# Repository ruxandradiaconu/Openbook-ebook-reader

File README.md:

OpenBook e-book reader
Diaconu Oana-Ruxandra - 331CC

## Diagrama bloc

## BOM – Bill of Materials

| Componenta                                                | Link                                                                                             | Datasheet                                                                                                                              |
|:----------------------------------------------------------|:-------------------------------------------------------------------------------------------------|:---------------------------------------------------------------------------------------------------------------------------------------|
| 112A-TAAR-R03_ATTEND                                      | https://store.comet.bg/en/Catalogue/Product/43497/                                               | https://store.comet.bg/en/Catalogue/Product/43497/                                                                                     |
| 744043680IND_4828-WE-TPC_WRE                              | https://www.digikey.sg/en/models/1638515                                                         | https://www.digikey.sg/en/models/1638515                                                                                               |
| ADAFRUIT_LEDCHIP-LED0603                                  | https://www.snapeda.com/parts/KP-1608SURCK/Kingbright/view-part/?ref=search&t=LED%200603         | https://www.snapeda.com/parts/KP-1608SURCK/Kingbright/datasheet/                                                                       |
| BD5229G-TR                                                | https://componentsearchengine.com/part-view/BD5229G-TR/ROHM%20Semiconductor                      | https://componentsearchengine.com/part-view/BD5229G-TR/ROHM%20Semiconductor                                                            |
| BME680                                                    | https://www.snapeda.com/parts/BME680/Bosch/view-part/?welcome=home                               | https://www.snapeda.com/parts/BME680/Bosch%20Sensortec/datasheet/                                                                      |
| BUTTON_CUSYOMV1                                           | https://industry.panasonic.com/global/en/downloads?tab=cad&small_g_cd=203&part_no=EVQPUJ02K      | https://industry.panasonic.com/global/en/downloads?tab=catalog&small_g_cd=203&part_no=EVQPUJ02K                                        |
| CC0402MRX5R5BB106                                           | https://componentsearchengine.com/part-view/CC0402MRX5R5BB106/YAGEO      | https://componentsearchengine.com/part-view/CC0402MRX5R5BB106/YAGEO                                        |
| CPH3225A                                                  | https://www.snapeda.com/parts/CPH3225A/Seiko+Instruments/view-part/?ref=eda                      | https://www.snapeda.com/parts/CPH3225A/Seiko%20Instruments/datasheet/                                                                  |
| DS3231SN                                                  | https://www.snapeda.com/parts/DS3231SN%23/Analog+Devices/view-part/?ref=eda                      | https://www.snapeda.com/parts/DS3231SN%23/Analog%20Devices/datasheet/                                                                  |
| 7.5in E-ink Display                                                  | https://grabcad.com/library/7-5in-e-ink-display-assortment-1                      | https://grabcad.com/library/7-5in-e-ink-display-assortment-1                                                                  |
| ESP32-C6-WROOM-1-N8                                       | https://www.snapeda.com/parts/ESP32-C6-WROOM-1-N8/Espressif+Systems/view-part/?ref=eda           | https://www.snapeda.com/parts/ESP32-C6-WROOM-1-N8/Espressif%20Systems/datasheet/                                                       |
| ESP32C6_VARISTORCN1812                                    | https://www.mouser.co.uk/ProductDetail/EPCOS-TDK/B72520T0350K062                                 | https://www.mouser.co.uk/ProductDetail/EPCOS-TDK/B72520T0350K062                                                      |
| ESP32_WROVER_BME680_BME680                                | https://www.snapeda.com/parts/BME680/Bosch/view-part/?welcome=home                               | https://www.snapeda.com/parts/BME680/Bosch%20Sensortec/datasheet/                                                                      |
| ESP32_WROVER_EAGLE-LTSPICE_CC0402                         | https://componentsearchengine.com/part-view/CC0402MRX5R5BB106/YAGEO                              | https://componentsearchengine.com/Datasheets/2/CC0402MRX5R5BB106.pdf                                                                   |
| ESP32_WROVER_EAGLE-LTSPICE_RR0402                         | https://www.snapeda.com/parts/RC0402FR-07226RL/Yageo/view-part/                                  | https://www.snapeda.com/parts/RC0402FR-07226RL/Yageo/datasheet/                                                                        |
| ESP32_WROVER_SPARKFUN-DISCRETESEMI_MOSFET_PCH-DMG2305UX-7 | https://componentsearchengine.com/part-view/DMG2305UX-7/Diodes%20Incorporated                    | https://componentsearchengine.com/part-view/DMG2305UX-7/Diodes%20Incorporated                                                                                |
| FH34SRJ-24S-0.5SH_99_                                     | https://componentsearchengine.com/part-view/XC6220A331MR-G/Torex                                 |  https://componentsearchengine.com/part-view/XC6220A331MR-G/Torex                                                                           |
| MAX17048G+T10                                             | https://www.snapeda.com/parts/MAX17048G+T10/Analog+Devices/view-part/?ref=eda                    | https://www.snapeda.com/parts/MAX17048G+T10/Analog%20Devices/datasheet/                                                                |
| MBR0530                                                   | https://ro.mouser.com/ProductDetail/KYOCERA-AVX/SD0805S020S1R0                                   | https://ro.mouser.com/datasheet/2/40/schottky-3165252.pdf                                                                              |
| MCP73831                                                  | https://www.digikey.com/en/models/1874108                                                        | https://www.digikey.com/en/models/1874108 |
| PGB1010603MR                                              | https://www.snapeda.com/parts/PGB1010603MR/Littelfuse/view-part/?ref=eda                         | https://www.snapeda.com/parts/PGB1010603MR/Littelfuse%20Inc./datasheet/                                                                |
| QWIIC_CONNECTORJS-1MM                                     | https://www.snapeda.com/parts/PRT-14417/SparkFun/view-part/                                      | https://www.snapeda.com/parts/PRT-14417/SparkFun%20Electronics/datasheet/                                                              |
| RCL-CT3528                              | https://stud33302.autodesk360.com/g/shares/SH30dd5QT870c25f12fc6065d74bcaa3bf24                                                         | https://stud33302.autodesk360.com/g/shares/SH30dd5QT870c25f12fc6065d74bcaa3bf24                                                                                               |
| SAMACSYS_PARTS_USB4110-GF-A                               | https://componentsearchengine.com/part-view/USB4110-GF-A/GCT%20(GLOBAL%20CONNECTOR%20TECHNOLOGY) | https://componentsearchengine.com/part-view/USB4110-GF-A/GCT%20(GLOBAL%20CONNECTOR%20TECHNOLOGY)                                                                                              |
| SI1308EDL-T1-GE3                                          | https://componentsearchengine.com/part-view/SI1308EDL-T1-GE3/Vishay                              | https://componentsearchengine.com/Datasheets/1/SI1308EDL-T1-GE3.pdf                                                                    |
| SJ                                                        | https://grabcad.com/library/solder-jumpers-1                                                     | https://grabcad.com/library/solder-jumpers-1                                                                                           |
| USBLC6-2SC6Y                                              | https://www.snapeda.com/parts/USBLC6-2SC6Y/STMicroelectronics/view-part/?ref=eda                 | https://www.snapeda.com/parts/USBLC6-2SC6Y/STMicroelectronics/datasheet/                                                               |
| W25Q512JVEIQ                                              | https://www.snapeda.com/parts/W25Q512JVEIQ/Winbond+Electronics/view-part/?ref=eda                | https://www.snapeda.com/parts/W25Q512JVEIQ/Winbond%20Electronics/datasheet/                                                            |
| XC6220A331MR-G                                            | https://componentsearchengine.com/part-view/XC6220A331MR-G/Torex                                 | https://componentsearchengine.com/part-view/XC6220A331MR-G/Torex                                                                           |

## Descriere functionalitati hardware

###  **E-paper Display**
  - Conectat prin pinii MOSI, SCK, CS, DC, BUSY, RST
  - Permite afișarea conținutului static cu consum energetic extrem de redus
  
###  **SD Card**
  - Conectat prin CS, MOSI, MISO, SCK
  - Utilizat pentru stocarea cărților electronice și a configurațiilor

###  **Baterie Li-Po + Fuel Gauge**
  - Alimentarea principală a sistemului, conectată direct prin paduri la PCB
  - Monitorizată prin MAX17048G+T10 conectat pe I2C (SDA, SCL)

###  **BME688**
  - Senzor ambiental pentru temperatură, presiune, umiditate și gaze
  - Comunică prin aceiași pini I2C ca RTC și Fuel Gauge

###  **RTC** 
  - Oferă timp real precis, cu pin INT pentru întreruperi și pin de reset 
  - Alimentat separat prin VRTC

###  **Butoane fizice**
  - BOOT, IO_CHANGE și RESET
  - Permite controlul funcțiilor precum trecerea între pagini, pornirea dispozitivului, sau activarea bootloader-ului pentru upload firmware

###  **USB-C Conector**
  - Permite programarea și încărcarea dispozitivului.
  - Include protecții ESD și varistor pentru protecția circuitului.

### Specificații de comunicație:

- **SPI** pentru SD card, display și memorie NOR Flash.
- **I2C** pentru RTC, senzor BME688 și fuel gauge.
- **UART** pentru debug sau comunicație serială externă.

### Estimare consum:

- În regim activ: între 80–150 mA (în funcție de e-paper și senzorii activi).
- În standby (deep sleep): sub 1 mA.
- Display-ul e-paper nu consumă curent în regim static – doar la refresh.

## Corespondenta pini ESP32-C6 - restul componentelor

| Pin ESP32-C6 | Nume net / semnal     | Componentă asociată        | Funcție / Motivare                                  |
|--------------|------------------------|-----------------------------|-----------------------------------------------------|
| GPIO0        | IO/BOOT                | Buton BOOT                  | Activare bootloader pentru flash                    |
| GPIO1        | SS_SD                  | SD Card                     | Chip select pentru card SD                          |
| GPIO3        | MOSI                   | SD Card + E-Paper           | Comunicare SPI                                      |
| GPIO4        | MISO                   | SD Card                     | Citire date SPI                                     |
| GPIO5        | SCK                    | SD Card + E-Paper           | Clock SPI                                           |
| GPIO6        | EPD_CS                 | E-Paper Display             | Selectare ecran SPI                                 |
| GPIO7        | EPD_DC                 | E-Paper Display             | Data/Command pentru ecran                           |
| GPIO8        | EPD_BUSY               | E-Paper Display             | Semnal BUSY de la ecran                             |
| GPIO9        | EPD_RST                | E-Paper Display             | Reset hardware ecran                                |
| GPIO10       | FLASH_CS               | NOR Flash W25Q512           | Chip select memorie SPI                             |
| GPIO16       | TXD0                   | UART Serial                 | Transmisie serială                                  |
| GPIO17       | RXD0                   | UART Serial                 | Recepție serială                                    |
| GPIO18       | SDA                    | RTC, BME688, Fuel Gauge     | I2C Data                                            |
| GPIO19       | SCL                    | RTC, BME688, Fuel Gauge     | I2C Clock                                           |
| GPIO20       | INT_RTC                | RTC                         | Interrupere alarmă                                  |
| GPIO21       | IO/CHANGE              | Buton IO_CHANGE             | Detecție apăsare buton                              |
| GPIO22       | RTC_RST                | RTC                         | Reset RTC                                           |
| GPIO23       | VRTC                   | RTC                         | Tensiune RTC                                        |
| GPIO44       | RESE                   | Reset ESP / Sisteme externe | Reset logic suplimentar                             |
| GPIO45       | GDR                    | E-Paper Driver              | Gate Driver enable                                  |

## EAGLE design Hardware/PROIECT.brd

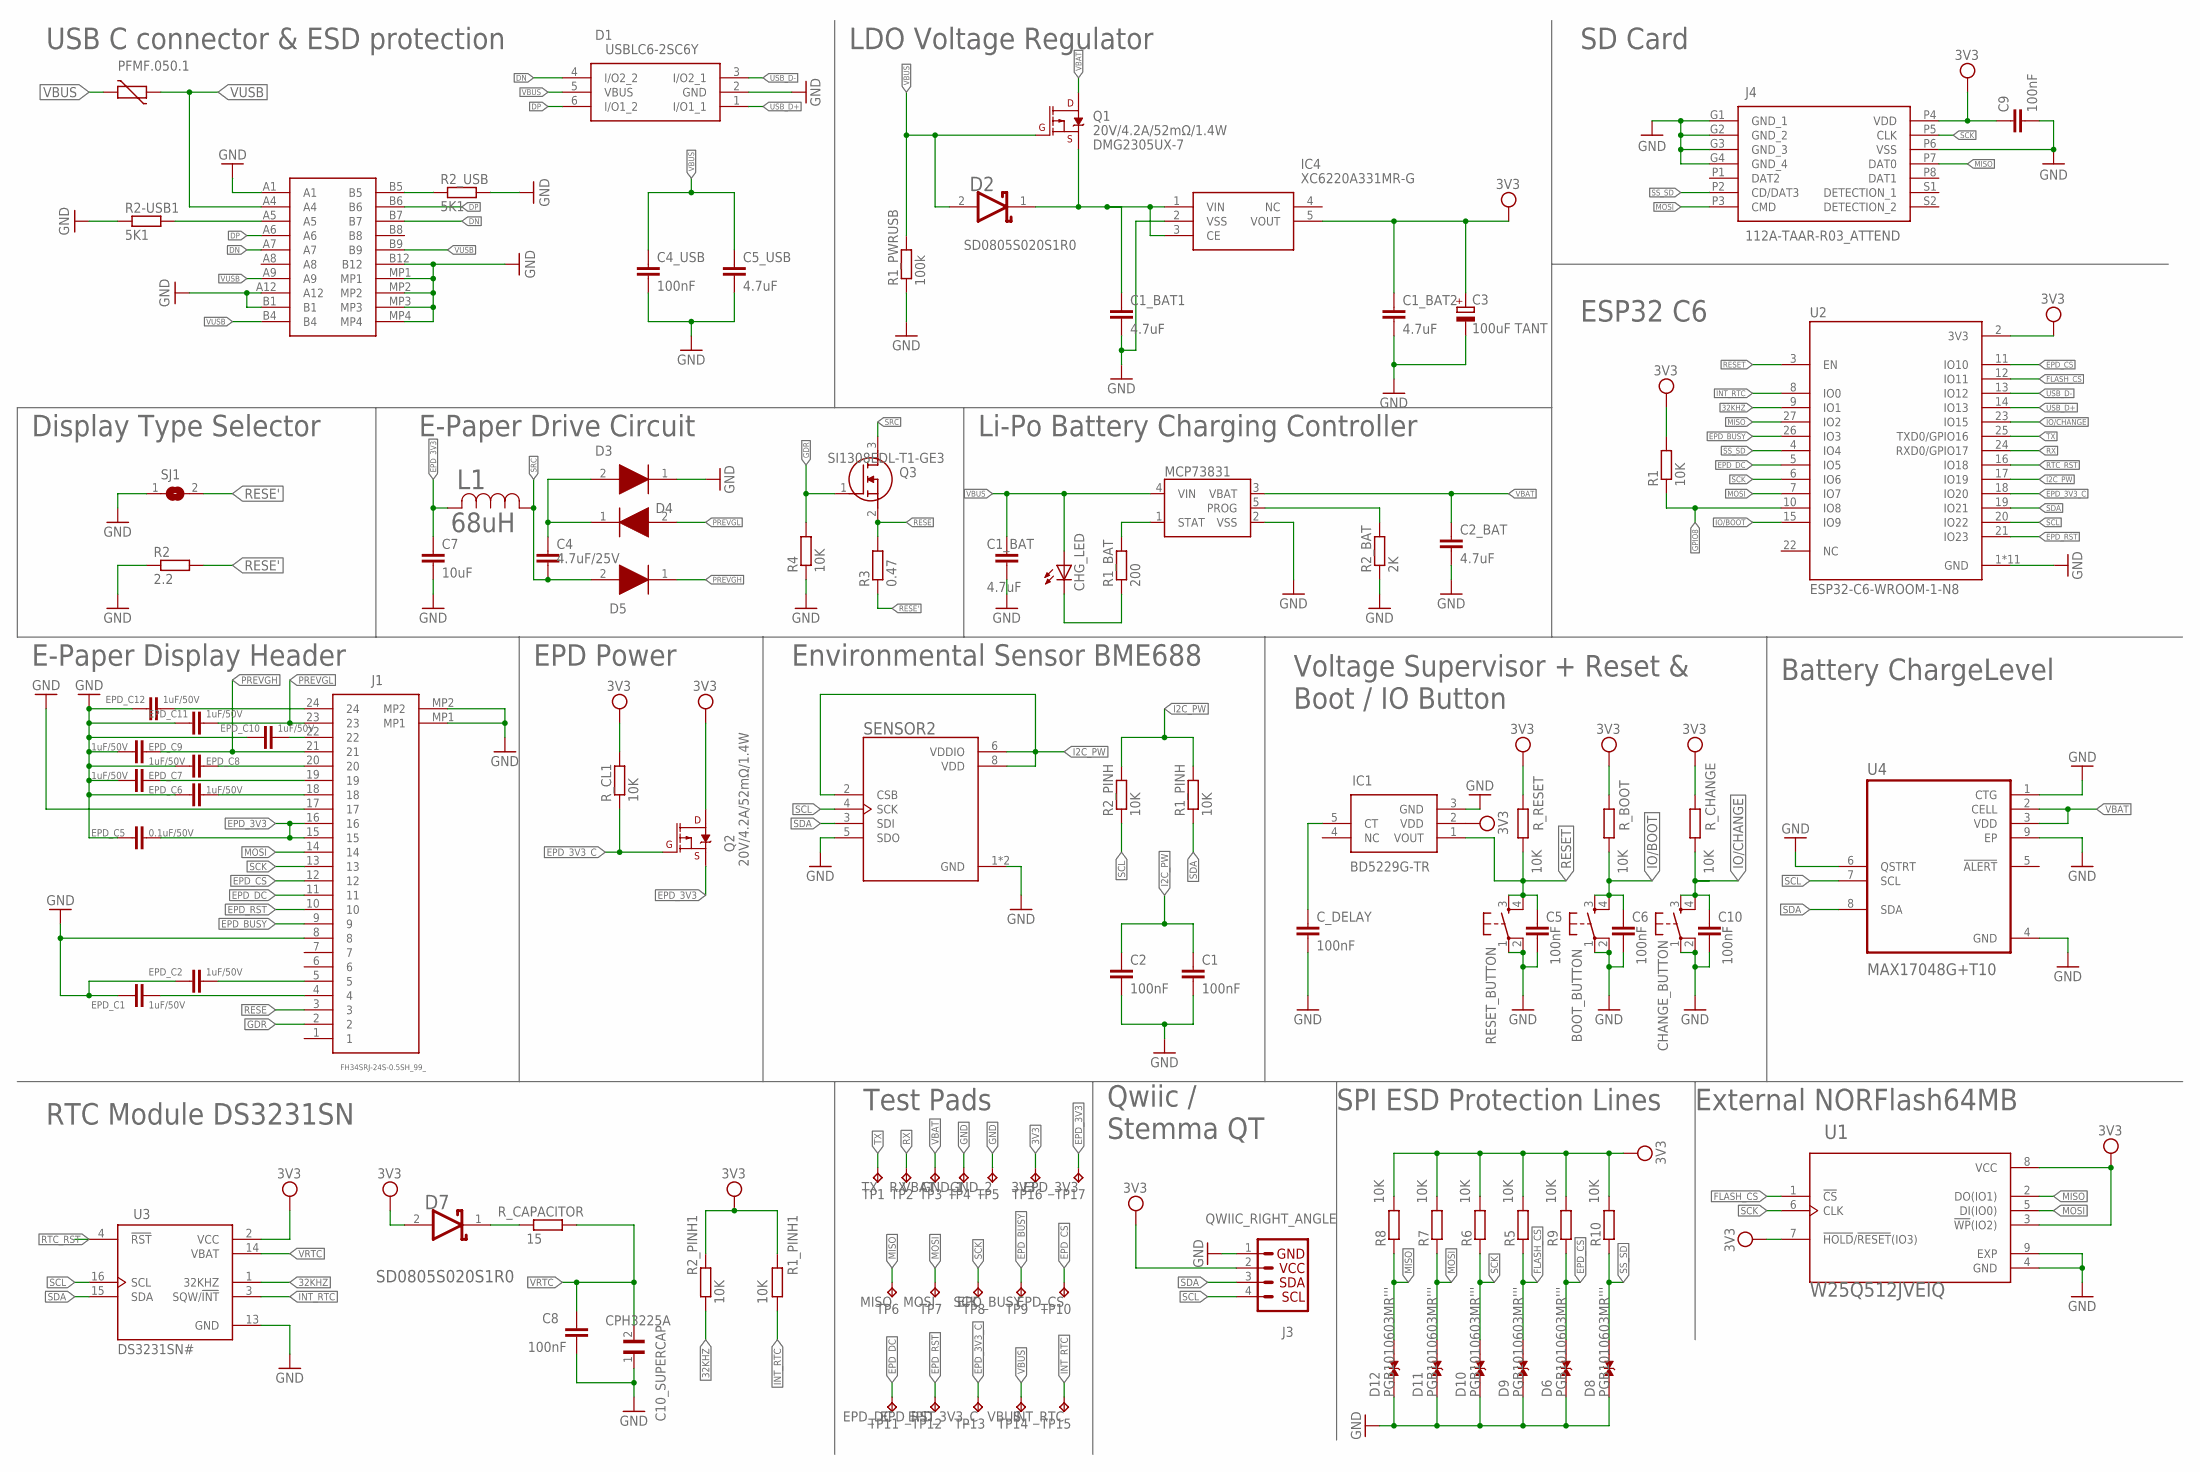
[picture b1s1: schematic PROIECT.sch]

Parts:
BOOT_BUTTON: BUTTON_CUSYOMV1; MYBUTTON
C1, C2, C4_USB: 100nF; ESP32_WROVER_EAGLE-LTSPICE_C0402
C1_BAT, C2_BAT: 4.7uF; EAGLE-LTSPICE_C0402
C1_BAT1, C1_BAT2, C5_USB: 4.7uF; ESP32_WROVER_EAGLE-LTSPICE_C0402
C3: 100uF TANT; RCL_CT3528
C4: 4.7uF/25V; EAGLE-LTSPICE_C0402
C5, C6, C8, C9, C10: 100nF; EAGLE-LTSPICE_C0402
C7: 10uF; EAGLE-LTSPICE_C0402
C10_SUPERCAP: CPH3225A; CAPCP3225X100N
CHANGE_BUTTON: BUTTON_CUSYOMV1; MYBUTTON
CHG_LED: ADAFRUIT_LEDCHIP-LED0603; ADAFRUIT_CHIP-LED0603
C_DELAY: 100nF; EAGLE-LTSPICE_C0402
D1: USBLC6-2SC6Y; SOT95P280X145-6N
D2, D7: ESP32_WROVER_AVX---SD0805S020S1R0_AVX_SD0805S020S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; ESP32_WROVER_AVX---SD0805S020S1R0_AVX_SD0805S020S1R0_0
D3, D4, D5: MBR0530'''; SOD3716X135N
D6, D8, D9, D10, D11, D12: PGB1010603MR'''; DIOC1608X36N
EPD_C1, EPD_C2, EPD_C6, EPD_C7, EPD_C8, EPD_C9, EPD_C10, EPD_C11, EPD_C12: 1uF/50V; EAGLE-LTSPICE_C0402
EPD_C5: 0.1uF/50V; EAGLE-LTSPICE_C0402
IC1: BD5229G-TR; SOT95P280X125-5N
IC4: XC6220A331MR-G; SOT95P280X120-5N
J1: FH34SRJ-24S-0.5SH_99_; FH34SRJ24S05SH99
J2: SAMACSYS_PARTS_USB4110-GF-A; SAMACSYS_PARTS_USB4110GFA
J3: QWIIC_RIGHT_ANGLE; JST04_1MM_RA
J4: 112A-TAAR-R03_ATTEND; 112ATAARR03ATTEND
L1: 68uH; IND_4828-WE-TPC_WRE
MCP73831: ESP32_WROVER_SPARKFUN-IC-POWER_MCP73831; ESP32_WROVER_SPARKFUN-IC-POWER_SOT23-5
PFMF.050.1: ESP32C6_VARISTORCN1812; ESP32C6_VARISTOR_CT/CN1812
Q1, Q2: 20V/4.2A/52mΩ/1.4W; ESP32_WROVER_SPARKFUN-DISCRETESEMI_SOT23-3
Q3: SI1308EDL-T1-GE3; SOT65P210X110-3N
R1, R1_PINH, R1_PINH1, R2_PINH, R2_PINH1, R4, R5, R6, R7, R8, R9, R10: 10K; ESP32_WROVER_EAGLE-LTSPICE_R0402
R1_BAT: 200; ESP32_WROVER_EAGLE-LTSPICE_R0402
R1_PWRUSB: 100k; ESP32_WROVER_EAGLE-LTSPICE_R0402
R2: 2.2; ESP32_WROVER_EAGLE-LTSPICE_R0402
R2-USB1, R2_USB: 5K1; ESP32_WROVER_EAGLE-LTSPICE_R0402
R2_BAT: 2K; ESP32_WROVER_EAGLE-LTSPICE_R0402
R3: 0.47; ESP32_WROVER_EAGLE-LTSPICE_R0402
RESET_BUTTON: BUTTON_CUSYOMV1; MYBUTTON
R_BOOT: 10K; ESP32_WROVER_EAGLE-LTSPICE_R0402
R_CAPACITOR: 15; ESP32_WROVER_EAGLE-LTSPICE_R0402
R_CHANGE: 10K; ESP32_WROVER_EAGLE-LTSPICE_R0402
R_CL1: 10K; ESP32_WROVER_EAGLE-LTSPICE_R0402
R_RESET: 10K; ESP32_WROVER_EAGLE-LTSPICE_R0402
SENSOR2: ESP32_WROVER_BME680_BME680; ESP32_WROVER_BME680_PSON80P300X300X100-8N
SJ1: SJ
TP1, TP2, TP3, TP4, TP5, TP6, TP7, TP8, TP9, TP10, TP11, TP12, TP13, TP14, TP15, TP16, TP17: TPTP20R; TP20R
U1: W25Q512JVEIQ; SON127P600X800X80-9N
U2: ESP32-C6-WROOM-1-N8; XCVR_ESP32-C6-WROOM-1-N8
U3: DS3231SN#; SOIC127P1032X265-16N
U4: MAX17048G+T10; SON50P200X200X80-9N

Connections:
3V3: C1_BAT2.1, C3.+, C9.1, D7.2 (ANODE), IC1.2 (VDD), IC4.5 (VOUT), J3.2, J4.P4 (VDD), Q2.3 (D), R1.2, R1_PINH1.2, R2_PINH1.2, R5.2, R6.2, R7.2, R8.2, R9.2, R10.2, R_BOOT.2, R_CHANGE.2, R_CL1.2, R_RESET.2, TP16.TP, U1.3 (!WP!(IO2)), U1.7 (!HOLD!/!RESET!(IO3)), U1.8 (VCC), U2.2 (3V3), U3.2 (VCC)
32KHZ: R2_PINH1.1, U2.9 (IO1), U3.1 (32KHZ)
DN: D1.4 (I/O2_2), J2.A7, J2.B7
DP: D1.6 (I/O1_2), J2.A6, J2.B6
EPD_3V3: C7.1, EPD_C5.1, J1.15, J1.16, L1.2, Q2.2 (S), TP17.TP
EPD_3V3_C: Q2.1 (G), R_CL1.1, TP13.TP, U2.18 (IO20)
EPD_BUSY: J1.9, TP9.TP, U2.26 (IO3)
EPD_CS: D6.2, J1.12, R9.1, TP10.TP, U2.11 (IO10)
EPD_DC: J1.11, TP11.TP, U2.5 (IO5)
EPD_RST: J1.10, TP12.TP, U2.21 (IO23)
FLASH_CS: D9.2, R5.1, U1.1 (!CS), U2.12 (IO11)
GDR: J1.2, Q3.1 (G), R4.2
GND: BOOT_BUTTON.1, BOOT_BUTTON.2, C1.2, C1_BAT.2, C1_BAT1.2, C1_BAT2.2, C2.2, C2_BAT.2, C3.-, C4_USB.2, C5.2, C5_USB.2, C6.2, C7.2, C8.2, C9.2, C10.2, C10_SUPERCAP.1, CHANGE_BUTTON.1, CHANGE_BUTTON.2, C_DELAY.2, D1.2 (GND), D3.1 (K), D6.1, D8.1, D9.1, D10.1, D11.1, D12.1, EPD_C1.2, EPD_C2.2, EPD_C5.2, EPD_C6.2, EPD_C7.2, EPD_C8.2, EPD_C9.2, EPD_C10.2, EPD_C11.2, EPD_C12.2, IC1.3 (GND), IC4.2 (VSS), J1.8, J1.17, J1.MP1, J1.MP2, J2.A1, J2.A12, J2.B1, J2.B12, J2.MP1, J2.MP2, J2.MP3, J2.MP4, J3.1, J4.G1 (GND_1), J4.G2 (GND_2), J4.G3 (GND_3), J4.G4 (GND_4), J4.P6 (VSS), MCP73831.2 (VSS), R1_PWRUSB.1, R2.1, R2-USB1.1, R2_BAT.1, R2_USB.2, R4.1, RESET_BUTTON.1, RESET_BUTTON.2, SENSOR2.1 (GND), SENSOR2.5 (SDO), SENSOR2.7 (GND), SJ1.1, TP4.TP, TP5.TP, U1.4 (GND), U1.9 (EXP), U2.1 (GND), U2.28 (GND), U2.29_1 (GND), U2.29_2 (GND), U2.29_3 (GND), U2.29_4 (GND), U2.29_5 (GND), U2.29_6 (GND), U2.29_7 (GND), U2.29_8 (GND), U2.29_9 (GND), U3.13 (GND), U4.1 (CTG), U4.4 (GND), U4.6 (QSTRT), U4.9 (EP)
GPIO8: R1.1, U2.10 (IO8)
I2C_PW: C1.1, C2.1, R1_PINH.2, R2_PINH.2, SENSOR2.2 (CSB), SENSOR2.6 (VDDIO), SENSOR2.8 (VDD), U2.17 (IO19)
INT_RTC: R1_PINH1.1, TP15.TP, U2.8 (IO0), U3.3 (SQW/!INT)
IO/BOOT: BOOT_BUTTON.3, BOOT_BUTTON.4, C6.1, R_BOOT.1, U2.15 (IO9)
IO/CHANGE: C10.1, CHANGE_BUTTON.3, CHANGE_BUTTON.4, R_CHANGE.1, U2.23 (IO15)
MISO: D12.2, J4.P7 (DAT0), R8.1, TP6.TP, U1.2 (DO(IO1)), U2.27 (IO2)
MOSI: D11.2, J1.14, J4.P3 (CMD), R7.1, TP7.TP, U1.5 (DI(IO0)), U2.7 (IO7)
unnamed: J2.B5, R2_USB.1
unnamed: J2.A5, R2-USB1.2
unnamed: MCP73831.1 (STAT), R1_BAT.2
unnamed: CHG_LED.C, R1_BAT.1
unnamed: C_DELAY.1, IC1.5 (CT)
unnamed: C1_BAT1.1, D2.1 (CATHODE), IC4.1 (VIN), IC4.3 (CE), Q1.2 (S)
unnamed: MCP73831.5 (PROG), R2_BAT.2
unnamed: C4.1, D3.2 (A), D4.1 (K)
unnamed: EPD_C10.1, J1.22
unnamed: EPD_C1.1, J1.4
unnamed: EPD_C12.1, J1.24
unnamed: EPD_C8.1, J1.20
unnamed: EPD_C7.1, J1.19
unnamed: D7.1 (CATHODE), R_CAPACITOR.1
unnamed: EPD_C6.1, J1.18
unnamed: EPD_C2.1, J1.5
PREVGH: D5.1 (K), EPD_C9.1, J1.21
PREVGL: D4.2 (A), EPD_C11.1, J1.23
RESE: J1.3, Q3.2 (S), R3.2
RESE': R2.2, R3.1, SJ1.2
RESET: C5.1, IC1.1 (VOUT), RESET_BUTTON.3, RESET_BUTTON.4, R_RESET.1, U2.3 (EN)
RTC_RST: U2.16 (IO18), U3.4 (!RST)
RX: TP2.TP, U2.24 (RXD0/GPIO17)
SCK: D10.2, J1.13, J4.P5 (CLK), R6.1, TP8.TP, U1.6 (CLK), U2.6 (IO6)
SCL: J3.4, R2_PINH.1, SENSOR2.4 (SCK), U2.20 (IO22), U3.16 (SCL), U4.7 (SCL)
SDA: J3.3, R1_PINH.1, SENSOR2.3 (SDI), U2.19 (IO21), U3.15 (SDA), U4.8 (SDA)
SRC: C4.2, D5.2 (A), L1.1, Q3.3 (D)
SS_SD: D8.2, J4.P2 (CD/DAT3), R10.1, U2.4 (IO4)
TX: TP1.TP, U2.25 (TXD0/GPIO16)
USB_D+: D1.1 (I/O1_1), U2.14 (IO13)
USB_D-: D1.3 (I/O2_1), U2.13 (IO12)
VBAT: C2_BAT.1, MCP73831.3 (VBAT), Q1.3 (D), TP3.TP, U4.2 (CELL), U4.3 (VDD)
VBUS: C1_BAT.1, C4_USB.1, C5_USB.1, CHG_LED.A, D1.5 (VBUS), D2.2 (ANODE), MCP73831.4 (VIN), PFMF.050.1.2, Q1.1 (G), R1_PWRUSB.2, TP14.TP
VRTC: C8.1, C10_SUPERCAP.2, R_CAPACITOR.2, U3.14 (VBAT)
VUSB: J2.A4, J2.A9, J2.B4, J2.B9, PFMF.050.1.1

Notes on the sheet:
SD0805S020S1R0
DMG2305UX-7
USB C connector & ESD protection
LDO Voltage Regulator
SD Card
ESP32 C6
Li-Po Battery Charging Controller
E-Paper Drive Circuit
Display Type Selector
E-Paper Display Header
RTC Module DS3231SN
EPD Power
Environmental Sensor BME688
Test Pads
Qwiic / Stemma QT
Voltage Supervisor + Reset & Boot / IO Button
SPI ESD Protection Lines
Battery ChargeLevel
External NORFlash64MB

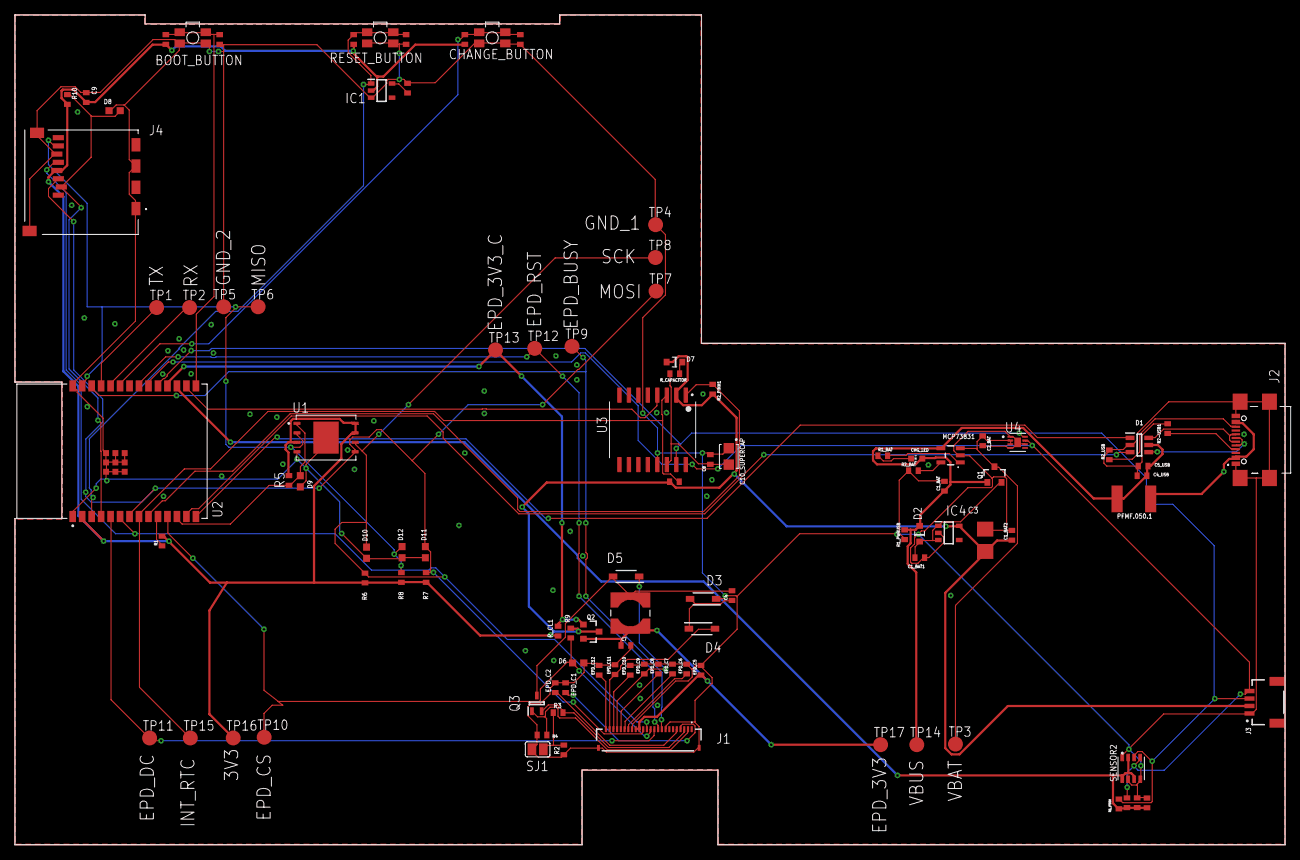
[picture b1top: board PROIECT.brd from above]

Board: 2 copper layers, 170.2 x 111.2 mm, 103 parts (0 on the bottom side), 55 nets.

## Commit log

2025-04-06 Create LICENSE
2025-04-11 update files after issues
2025-04-11 files after review
2025-04-11 completed project after review
2025-04-11 added exploded view
2025-04-11 Added in BOM C3 component & display

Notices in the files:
parts and their libraries:
COPYRIGHT: Copyright (C) 2024 Ultra Librarian. All rights reserved.
